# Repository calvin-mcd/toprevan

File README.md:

# toprevan

The toprevan is a EC (topre) pcb for trashman's [minivan](https://trashman.wiki/keyboards/minivan) keyboad. The pcb supports the [minisub](https://trashman.wiki/community/pcbs/minisub) layout with both the 625U spacebar and the split 275U, 225U spacebars. The pcb has some of the traymout holes of the original minivan pcb but topre housings (and potentially some domes) need cutting to make that work.

Each layout requires its own respective plate. Various plate files can be found in the production folder. But since there are many different plate styles for the various cases out there, beware that plates could not have been tested beforehand.

***VERSIONS***:
In the production folder you will find both the prototype production files and the revision files (as well as various plate files). Please be aware when ordering pcbs of their differences and what aspects have not been confirmed to work yet.
- The prototype is sporting a standard usb port which limits case compatibility a bit but using o-rings like on the travaulta should mitigate that in a bunch of cases. The rgb breakout has not been tested. Otherwise the pcb is fully working.
- The revision is using another USB port for more compatibility. It also sports all of the traymount holes. The rgb breakout has still not been tested. The revision has not been prototyped yet.

## Layout

[Link](https://www.keyboard-layout-editor.com/#/gists/1fa1f216f42ccb54e6a5849ecc492d73)

## Firmware

The basic EC firmware is ready to go and the source code is provided for tweaking any settings.

## Plates & Hardware

Plate files are available for OEM (original and deskey housings), for each respective bottom row choice, and for the original plate, Hull and Embrace cases.

Furthermore, you will need 22x 10mm M2 screws and M2 nuts to assemble the pcb. O-rings might help aligning the pcb and usb port in some cases, but is not required.

## Disclaimer

Please note that this project is a work in progress with no guarantees of a working outcome. No-one involved in this project is responsible for any usage issues that may arise. Order at your own risk. Support will not be provided but pull requests will be reviewed and possibly accepted.

## License

Shield: 

This work is licensed under a  
[Creative Commons Attribution-NonCommercial-ShareAlike 4.0 International License](http://creativecommons.org/licenses/by-nc-sa/4.0/).

## Credits

big thanks to petejohanson for feedback and help!

Furthermore, many thanks for feedback, help, references go to Sporkus, Cipulot\#8455 & matthewdias\#2671.

Any questions, contact Calvin0563 on Discord.

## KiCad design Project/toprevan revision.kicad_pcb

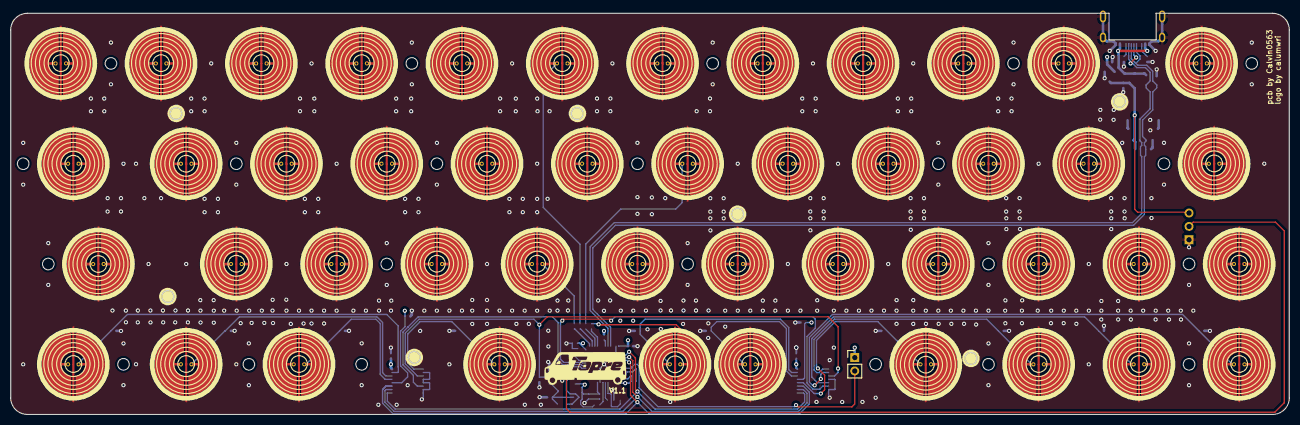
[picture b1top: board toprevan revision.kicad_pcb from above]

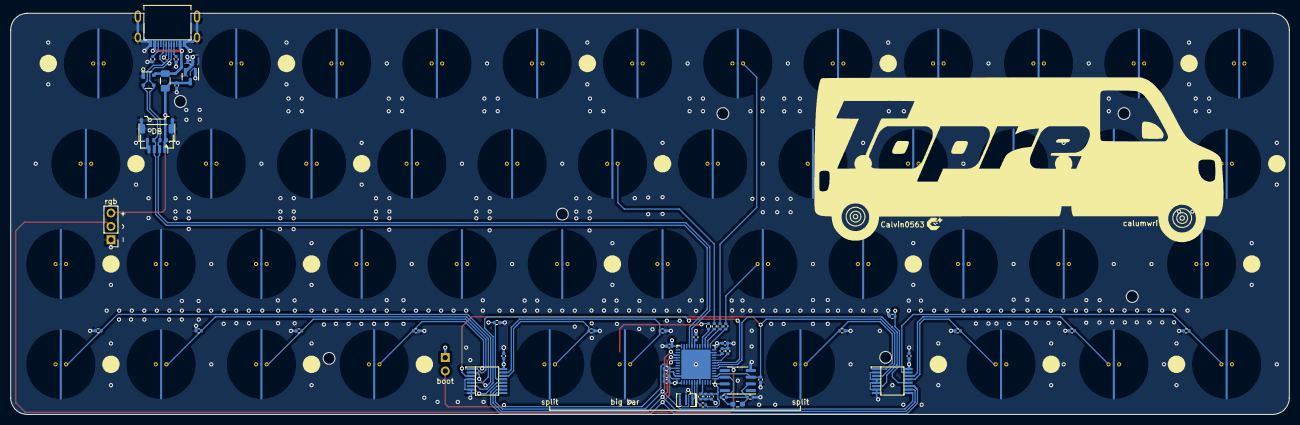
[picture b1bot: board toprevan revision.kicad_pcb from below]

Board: 4 copper layers, 242.9 x 76.2 mm, 119 parts (50 on the bottom side), 44 nets.

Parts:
C1: 4.7u; C_0402_1005Metric
C6, C7, C8, C9, C10, C14, C16, C17: 100n; C_0402_1005Metric
C11, C12, C13: 1u; C_0402_1005Metric
C15: 220p; C_0402_1005Metric
D1: PRTR5V0U2X; SOT-143
F_USBC1: 500mA; Fuse_1206_3216Metric
H1, H2, H3, H4, H5, H6, H7, H8, H9, H10, H11, H12, H13, H14, H15, H16, H17, H18, H19, H20, H21, H22: MountingHole; HOLE_M2
J1: JST SH; JST_SH_SM04B-SRSS-TB_1x04-1MP_P1.00mm_Horizontal
J2: Pico EZmate; Molex_Pico-EZmate_78171-0004_1x04-1MP_P1.20mm_Vertical
J4: ARGB; PinHeader_1x03_P2.54mm_Vertical
J5: USB_C sink board 1.3mm; USB4510031A
JP1: Ext_Res; R_0603_1608Metric_Pad0.98x0.95mm_HandSolder
R2, R12, R13, R14, R15, R16, R17, R19, R20, R21, R22, R23, R24, R25: 100k; R_0402_1005Metric
R3, R4, R5, R6: 100; R_0402_1005Metric
R7, R8: 5k1; R_0402_1005Metric
R9, R10, R11: 10k; R_0402_1005Metric
R18: 1k; R_0402_1005Metric
SW1: BOOT0; PinHeader_1x02_P2.54mm_Vertical
SW_EC1, SW_EC2, SW_EC3, SW_EC4, SW_EC5, SW_EC6, SW_EC7, SW_EC8, SW_EC9, SW_EC10, SW_EC11, SW_EC12, SW_EC13, SW_EC14, SW_EC15, SW_EC16, SW_EC17, SW_EC18, SW_EC19, SW_EC20, SW_EC21, SW_EC22, SW_EC23, SW_EC24, SW_EC25, SW_EC26, SW_EC27, SW_EC28, SW_EC29, SW_EC30, SW_EC31, SW_EC32, SW_EC33, SW_EC34, SW_EC35, SW_EC36, SW_EC37, SW_EC38, SW_EC39, SW_EC40, SW_EC41, SW_EC42, SW_EC43, SW_EC44, SW_EC45, SW_EC46: Topre; ecs_pad_1U_no_ring
U1: STM32F401CBUx; QFN-48-1EP_7x7mm_P0.5mm_EP5.6x5.6mm
U3: XC6206PxxxMR; SOT-23
U4, U6: 74HC4051; TSSOP16
U5: OPA350; SOIC-8_3.9x4.9mm_P1.27mm
Y1: 8 MHz; Resonator_SMD_Murata_CSTxExxV-3Pin_3.0x1.1mm

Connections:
+5V: C12.1, F_USBC1.2, J1.1, J2.1, J4.3, U3.3 (VI)
/CC1: J5.A5 (CC1), R7.1
/CC2: J5.B5 (CC2), R8.1
ADC: JP1.1 (A), R12.2, U1.13 (PA3), U5.6 (OUT)
AMUX_SEL_0: U1.41 (PB5), U4.11 (S0), U6.11 (S0)
AMUX_SEL_1: U1.40 (PB4), U4.10 (S1), U6.10 (S1)
AMUX_SEL_2: U1.39 (PB3), U4.9 (S2), U6.9 (S2)
APLEX_EN_PIN_0: U1.18 (PB0), U4.6 (~E)
APLEX_EN_PIN_1: U1.19 (PB1), U6.6 (~E)
APLEX_OUT_PIN_0: C15.2, U1.14 (PA4), U4.3 (A), U5.3 (IN+), U6.3 (A)
ARGB_3V3: J4.2, U1.17 (PA7)
BOOT0: R11.1, SW1.2 (B), U1.44 (BOOT0)
BOOT1: R10.2, U1.20 (PB2)
COL0: R15.1, SW_EC1.2, SW_EC13.2, SW_EC25.2, SW_EC37.2, U4.15 (A2)
COL1: R14.1, SW_EC2.2, SW_EC14.2, SW_EC26.2, SW_EC38.2, U4.14 (A1)
COL2: R13.1, SW_EC3.2, SW_EC15.2, SW_EC27.2, SW_EC39.2, U4.13 (A0)
COL3: R16.1, SW_EC4.2, SW_EC16.2, SW_EC28.2, U4.12 (A3)
COL4: R17.1, SW_EC5.2, SW_EC17.2, SW_EC29.2, SW_EC40.2, U4.1 (A4)
COL5: R21.1, SW_EC6.2, SW_EC18.2, SW_EC30.2, SW_EC41.2, U6.15 (A2)
COL6: R20.1, SW_EC7.2, SW_EC19.2, SW_EC31.2, SW_EC42.2, U6.14 (A1)
COL7: R19.1, SW_EC8.2, SW_EC20.2, SW_EC32.2, U6.13 (A0)
COL8: R22.1, SW_EC9.2, SW_EC21.2, SW_EC33.2, SW_EC43.2, U6.12 (A3)
COL9: R23.1, SW_EC10.2, SW_EC22.2, SW_EC34.2, SW_EC44.2, U6.1 (A4)
COL10: R24.1, SW_EC11.2, SW_EC23.2, SW_EC35.2, SW_EC45.2, U6.5 (A5)
COL11: R25.1, SW_EC12.2, SW_EC24.2, SW_EC36.2, SW_EC46.2, U6.2 (A6)
D+: D1.2 (I/O1), J1.3, J2.3, J5.A6 (D+), J5.B6 (D+), U1.33 (PA12)
D-: D1.3 (I/O2), J1.2, J2.2, J5.A7 (D-), J5.B7 (D-), U1.32 (PA11)
GND: C1.2, C6.2, C7.2, C8.2, C9.2, C10.2, C11.2, C12.2, C13.2, C14.2, C15.1, C16.2, C17.2, D1.1 (GND), J1.4, J1.MP (MountPin), J2.4, J2.MP (MountPin), J4.1, J5.A1 (GND), J5.A12 (GND), J5.S1 (SHIELD), R7.2, R8.2, R10.1, R11.2, R13.2, R14.2, R15.2, R16.2, R17.2, R18.2, R19.2, R20.2, R21.2, R22.2, R23.2, R24.2, R25.2, SW_EC1.3, SW_EC2.3, SW_EC3.3, SW_EC4.3, SW_EC5.3, SW_EC6.3, SW_EC7.3, SW_EC8.3, SW_EC9.3, SW_EC10.3, SW_EC11.3, SW_EC12.3, SW_EC13.3, SW_EC14.3, SW_EC15.3, SW_EC16.3, SW_EC17.3, SW_EC18.3, SW_EC19.3, SW_EC20.3, SW_EC21.3, SW_EC22.3, SW_EC23.3, SW_EC24.3, SW_EC25.3, SW_EC26.3, SW_EC27.3, SW_EC28.3, SW_EC29.3, SW_EC30.3, SW_EC31.3, SW_EC32.3, SW_EC33.3, SW_EC34.3, SW_EC35.3, SW_EC36.3, SW_EC37.3, SW_EC38.3, SW_EC39.3, SW_EC40.3, SW_EC41.3, SW_EC42.3, SW_EC43.3, SW_EC44.3, SW_EC45.3, SW_EC46.3, U1.8 (VSSA), U1.23 (VSS), U1.35 (VSS), U1.47 (VSS), U1.49 (VSS), U3.1 (GND), U4.2 (A6), U4.4 (A7), U4.5 (A5), U4.7 (VEE), U4.8 (GND), U5.4 (V-), U6.4 (A7), U6.7 (VEE), U6.8 (GND), Y1.2
NRST: R9.2, U1.7 (NRST)
unnamed: JP1.2 (B), R12.1, R18.1, U5.2 (IN-)
unnamed: R2.1, U1.31 (PA10)
unnamed: R6.2, U1.25 (PB12)
unnamed: R4.2, U1.26 (PB13)
unnamed: R5.2, U1.27 (PB14)
unnamed: R3.2, U1.28 (PB15)
unnamed: C1.1, U1.22 (VCAP1)
ROW0: R4.1, SW_EC1.1, SW_EC2.1, SW_EC3.1, SW_EC4.1, SW_EC5.1, SW_EC6.1, SW_EC7.1, SW_EC8.1, SW_EC9.1, SW_EC10.1, SW_EC11.1, SW_EC12.1
ROW1: R5.1, SW_EC13.1, SW_EC14.1, SW_EC15.1, SW_EC16.1, SW_EC17.1, SW_EC18.1, SW_EC19.1, SW_EC20.1, SW_EC21.1, SW_EC22.1, SW_EC23.1, SW_EC24.1
ROW2: R6.1, SW_EC25.1, SW_EC26.1, SW_EC27.1, SW_EC28.1, SW_EC29.1, SW_EC30.1, SW_EC31.1, SW_EC32.1, SW_EC33.1, SW_EC34.1, SW_EC35.1, SW_EC36.1
ROW3: R3.1, SW_EC37.1, SW_EC38.1, SW_EC39.1, SW_EC40.1, SW_EC41.1, SW_EC42.1, SW_EC43.1, SW_EC44.1, SW_EC45.1, SW_EC46.1
VBAT: C6.1, C7.1, C8.1, C9.1, C10.1, C11.1, C13.1, C14.1, C16.1, C17.1, R2.2, R9.1, SW1.1 (A), U1.1 (VBAT), U1.9 (VREF+), U1.24 (VDD), U1.36 (VDD), U1.48 (VDD), U3.2 (VO), U4.16 (VCC), U5.7 (V+), U6.16 (VCC)
VCC: D1.4 (VCC), F_USBC1.1, J5.A4 (VBUS), J5.A9 (VBUS)
XTAL0: U1.5 (PH0), Y1.3
XTAL1: U1.6 (PH1), Y1.1

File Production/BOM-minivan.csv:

Comment,Designator,Footprint,LCSC
1k,R18,R_0402_1005Metric,C11702
STM32F401CBUx,U1,QFN-48-1EP_7x7mm_P0.5mm_EP5.6x5.6mm,C118825
OPA350,U5,SOIC-8_3.9x4.9mm_P1.27mm,C13388
220p,C15,C_0402_1005Metric,C1530
JST SH,J1,JST_SH_SM04B-SRSS-TB_1x04-1MP_P1.00mm_Horizontal,C160404
USB_C_Receptacle_USB2.0,J3,USB_C_Receptacle_HRO_TYPE-C-31-M-12,C165948
4.7u,C1,C_0402_1005Metric,C23733
100,"R3,R4,R5,R6",R_0402_1005Metric,C25076
100k,"R12,R13,R14,R15,R16,R17,R19,R2,R20,R21,R22,R23,R24,R25",R_0402_1005Metric,C25741
10k,"R10,R11,R9",R_0402_1005Metric,C25744
5k1,"R7,R8",R_0402_1005Metric,C25905
PRTR5V0U2X,D1,SOT-143,C2827688
100n,"C10,C14,C16,C17,C6,C7,C8,C9",C_0402_1005Metric,C307331
1u,"C11,C12,C13",C_0402_1005Metric,C52923
XC6206PxxxMR,U3,SOT-23,C5446
74HC4051,"U4,U6",TSSOP16,C5645
500mA,F_USBC1,Fuse_1206_3216Metric,C70076
8 MHz,Y1,Resonator_SMD_Murata_CSTxExxV-3Pin_3.0x1.1mm,C907975

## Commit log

2024-05-13 initialise
2024-06-07 production files, plate files
2024-08-05 pcb & plate revision
    move mux, add cutout for all plates for boot
2024-08-11 review
2024-08-28 proto ready
2024-09-03 update & backup
2024-09-04 backup
2024-09-16 firmware wip
2024-11-26 plate generation
2024-12-22 publishing changes
2025-03-01 update
    before publishing
